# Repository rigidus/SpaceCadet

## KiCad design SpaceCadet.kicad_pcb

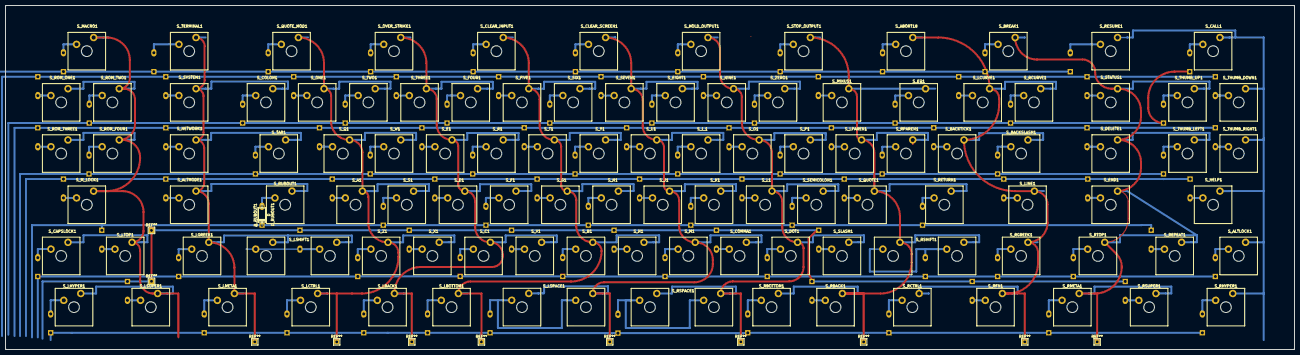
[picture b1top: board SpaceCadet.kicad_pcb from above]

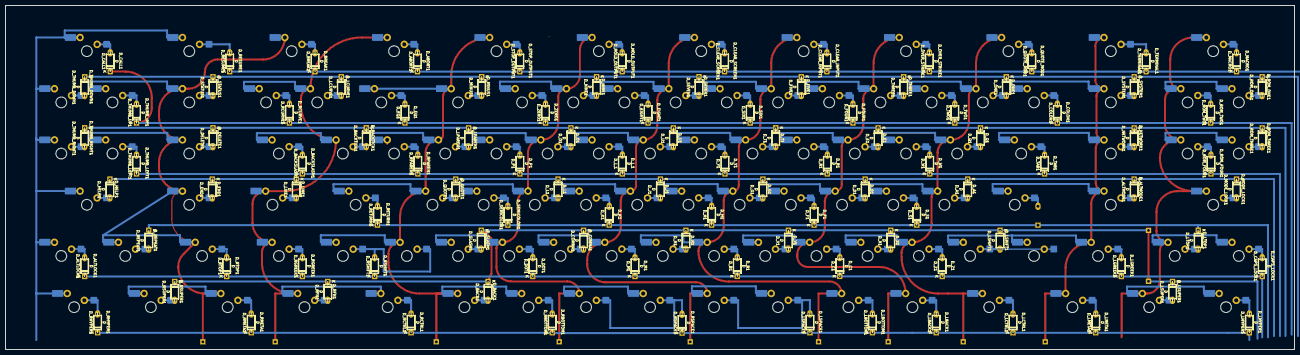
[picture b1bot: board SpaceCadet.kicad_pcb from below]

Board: 2 copper layers, 479.6 x 128.0 mm, 212 parts (105 on the bottom side), 127 nets.

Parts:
D_A1: D; D_P7.62mm
D_ABORT1: D; D_P7.62mm
D_ALTLOCK1: D; D_P7.62mm
D_ALTMODE1: D; D_P7.62mm
D_B1: D; D_P7.62mm
D_BACK1: D; D_P7.62mm
D_BACKSLASH1: D; D_P7.62mm
D_BACKTICK1: D; D_P7.62mm
D_BREAK1: D; D_P7.62mm
D_C1: D; D_P7.62mm
D_CALL1: D; D_P7.62mm
D_CAPS_LOCK1: D; D_P7.62mm
D_CLEAR_INPUT1: D; D_P7.62mm
D_CLEAR_SCREEN1: D; D_P7.62mm
D_COLON1: D; D_P7.62mm
D_COMMA1: D; D_P7.62mm
D_D1: D; D_P7.62mm
D_DELETE1: D; D_P7.62mm
D_DOT1: D; D_P7.62mm
D_E1: D; D_P7.62mm
D_EIGHT1: D; D_P7.62mm
D_END1: D; D_P7.62mm
D_EQ1: D; D_P7.62mm
D_F1: D; D_P7.62mm
D_FIVE1: D; D_P7.62mm
D_FOUR1: D; D_P7.62mm
D_G1: D; D_P7.62mm
D_H1: D; D_P7.62mm
D_HELP1: D; D_P7.62mm
D_HOLD_OUTPUT1: D; D_P7.62mm
D_I_1: D; D_P7.62mm
D_J1: D; D_P7.62mm
D_K1: D; D_P7.62mm
D_L1: D; D_P7.62mm
D_LBACK1: D; D_P7.62mm
D_LBOTTOM1: D; D_P7.62mm
D_LCTRL1: D; D_P7.62mm
D_LCURVE1: D; D_P7.62mm
D_LGREEK1: D; D_P7.62mm
D_LHYPER1: D; D_P7.62mm
D_LINE1: D; D_P7.62mm
D_LMETA1: D; D_P7.62mm
D_LPAREN1: D; D_P7.62mm
D_LSHIFT1: D; D_P7.62mm
D_LSPACE1: D; D_P7.62mm
D_LSUPER1: D; D_P7.62mm
D_LTOP1: D; D_P7.62mm
D_M1: D; D_P7.62mm
D_MACRO1: D; D_P7.62mm
D_MINUS1: D; D_P7.62mm
D_MODE_LOCK1: D; D_P7.62mm
D_N1: D; D_P7.62mm
D_NETWORK1: D; D_P7.62mm
D_NINE1: D; D_P7.62mm
D_O1: D; D_P7.62mm
D_ONE1: D; D_P7.62mm
D_OVER_STRIKE1: D; D_P7.62mm
D_P1: D; D_P7.62mm
D_Q1: D; D_P7.62mm
D_QUOTE1: D; D_P7.62mm
D_QUOTE_MOD1: D; D_P7.62mm
D_R1: D; D_P7.62mm
D_RBOTTOM1: D; D_P7.62mm
D_RCTRL1: D; D_P7.62mm
D_RCURVE1: D; D_P7.62mm
D_REPEAT1: D; D_P7.62mm
D_RESUME1: D; D_P7.62mm
D_RETURN1: D; D_P7.62mm
D_RFN1: D; D_P7.62mm
D_RGREEK1: D; D_P7.62mm
D_RHYPER1: D; D_P7.62mm
D_RMETA1: D; D_P7.62mm
D_ROM_FOUR1: D; D_P7.62mm
D_ROM_ONE1: D; D_P7.62mm
D_ROM_THREE1: D; D_P7.62mm
D_ROM_TWO1: D; D_P7.62mm
D_RPAREN1: D; D_P7.62mm
D_RSHIFT1: D; D_P7.62mm
D_RSPACE1: D; D_P7.62mm
D_RSUPER1: D; D_P7.62mm
D_RTOP1: D; D_P7.62mm
D_RUBOUT1: D; D_P7.62mm
D_S1: D; D_P7.62mm
D_SEMICOLON1: D; D_P7.62mm
D_SEVEN1: D; D_P7.62mm
D_SIX1: D; D_P7.62mm
D_SLASH1: D; D_P7.62mm
D_STATUS1: D; D_P7.62mm
D_STOP_OUTPUT1: D; D_P7.62mm
D_SYSTEM1: D; D_P7.62mm
D_T1: D; D_P7.62mm
D_TAB1: D; D_P7.62mm
D_TERMINAL1: D; D_P7.62mm
D_THREE1: D; D_P7.62mm
D_THUMB_DOWN1: D; D_P7.62mm
D_THUMB_LEFT1: D; D_P7.62mm
D_THUMB_RIGHT1: D; D_P7.62mm
D_THUMB_UP1: D; D_P7.62mm
D_TWO1: D; D_P7.62mm
D_U1: D; D_P7.62mm
D_V1: D; D_P7.62mm
D_W1: D; D_P7.62mm
D_X1: D; D_P7.62mm
D_Y1: D; D_P7.62mm
D_Z1: D; D_P7.62mm
D_ZERO1: D; D_P7.62mm
S_A1: A; SWMXK_1.00u
S_ABORT18: ABORT; SWMXK_2.00u
S_ALTLOCK1: ALT_LOCK; SWMXK_1.00u
S_ALTMODE1: ALTMODE; SWMXK_2.00u
S_B1: B; SWMXK_1.00u
S_BACKSLASH1: BACKSLASH; SWMXK_1.50u
S_BACKTICK1: BACKTICK; SWMXK_1.00u
S_BREAK1: BREAK; SWMXK_2.00u
S_C1: C; SWMXK_1.00u
S_CALL1: CALL; SWMXK_2.00u
S_CAPSLOCK1: CAPS_LOCK; SWMXK_1.00u
S_CLEAR_INPUT1: CLEAR_INPUT; SWMXK_2.00u
S_CLEAR_SCREEN1: CLEAR_SCREEN; SWMXK_2.00u
S_COLON1: COLON; SWMXK_1.00u
S_COMMA1: COMMA; SWMXK_1.00u
S_D1: D; SWMXK_1.00u
S_DELETE1: DELETE; SWMXK_2.00u
S_DOT1: DOT; SWMXK_1.00u
S_E1: E; SWMXK_1.00u
S_EIGHT1: EIGHT; SWMXK_1.00u
S_END1: END1; SWMXK_2.00u
S_EQ1: EQUAL; SWMXK_1.50u
S_F1: F; SWMXK_1.00u
S_FIVE1: FIVE; SWMXK_1.00u
S_FOUR1: FOUR; SWMXK_1.00u
S_G1: G; SWMXK_1.00u
S_H1: H; SWMXK_1.00u
S_HELP1: HELP; SWMXK_2.00u
S_HOLD_OUTPUT1: HOLD_OUTPUT; SWMXK_2.00u
S_I_1: I; SWMXK_1.00u
S_J1: J; SWMXK_1.00u
S_K1: K; SWMXK_1.00u
S_L1: L; SWMXK_1.00u
S_LBACK1: LBACK; SWMXK_1.25u
S_LBOTTOM1: LEFT_BOTTOM; SWMXK_1.25u
S_LCTRL1: LEFT_CTRL; SWMXK_1.75u
S_LCURVE1: LEFT_CURVE; SWMXK_1.00u
S_LGREEK1: LEFT_GREEK; SWMXK_1.50u
S_LHYPER1: LEFT_HYPER; SWMXK_1.50u
S_LINE1: LINE; SWMXK_1.25u
S_LMETA1: LEFT_META; SWMXK_1.50u
S_LPAREN1: LPAREN; SWMXK_1.00u
S_LSHIFT1: LEFT_SHIFT; SWMXK_2.25u
S_LSPACE1: LEFT_SPACE; SWMXK_2.75u
S_LSUPER1: LEFT_SUPER; SWMXK_1.50u
S_LTOP1: LEFT_TOP; SWMXK_1.50u
S_M1: M; SWMXK_1.00u
S_MACRO1: MACRO; SWMXK_2.00u
S_MINUS1: MINUS; SWMXK_1.50u
S_M_LOCK1: MODE_LOCK_1; SWMXK_2.00u
S_N1: N; SWMXK_1.00u
S_NETWORK1: NETWORK; SWMXK_2.00u
S_NINE1: NINE; SWMXK_1.00u
S_O1: O; SWMXK_1.00u
S_ONE1: ONE; SWMXK_1.00u
S_OVER_STRIKE1: OVER_STRIKE; SWMXK_2.00u
S_P1: P; SWMXK_1.00u
S_Q1: Q; SWMXK_1.00u
S_QUOTE1: QUOTE; SWMXK_1.00u
S_QUOTE_MOD1: QUOTE_MOD; SWMXK_2.00u
S_R1: R; SWMXK_1.00u
S_RBACK1: RIGHT_BACK; SWMXK_1.25u
S_RBOTTOM1: RIGHT_BOTTOM; SWMXK_1.25u
S_RCTRL1: RIGHT_CTRL; SWMXK_1.75u
S_RCURVE1: RIGHT_CURVE; SWMXK_1.00u
S_REPEAT1: REPEAT; SWMXK_1.50u
S_RESUME1: RESUME; SWMXK_2.00u
S_RETURN1: RETURN; SWMXK_2.00u
S_RFN1: RIGHT_FN; SWMXK_1.50u
S_RGREEK1: RIGHT_GREEK; SWMXK_1.50u
S_RHYPER1: RIGHT_HYPER; SWMXK_1.50u
S_RMETA1: RIGHT_META; SWMXK_1.50u
S_ROM_FOUR1: ROM_FOUR; SWMXK_1.00u
S_ROM_ONE1: ROM_ONE; SWMXK_1.00u
S_ROM_THREE1: ROM_THREE; SWMXK_1.00u
S_ROM_TWO1: ROM_TWO; SWMXK_1.00u
S_RPAREN1: RPAREN; SWMXK_1.00u
S_RSHIFT1: RIGHT_SHIFT; SWMXK_2.25u
S_RSPACE1: RIGHT_SPACE; SWMXK_2.25u
S_RSUPER1: RIGHT_SUPER; SWMXK_1.50u
S_RTOP1: RIGHT_TOP; SWMXK_1.50u
S_RUBOUT1: RUBOUT; SWMXK_1.75u
S_S1: S; SWMXK_1.00u
S_SEMICOLON1: SEMICOLON; SWMXK_1.00u
S_SEVEN1: SEVEN; SWMXK_1.00u
S_SIX1: SIX; SWMXK_1.00u
S_SLASH1: SLASH; SWMXK_1.00u
S_STATUS1: STATUS; SWMXK_2.00u
S_STOP_OUTPUT1: STOP_OUTPUT; SWMXK_2.00u
S_SYSTEM1: SYSTEM; SWMXK_2.00u
S_T1: T; SWMXK_1.00u
S_TAB1: TAB; SWMXK_1.50u
S_TERMINAL1: TERMINAL; SWMXK_2.00u
S_THREE1: THREE; SWMXK_1.00u
S_THUMB_DOWN1: THUMB_DOWN; SWMXK_1.00u
S_THUMB_LEFT1: THUMB_LEFT; SWMXK_1.00u
S_THUMB_RIGHT1: THUMB_RIGHT; SWMXK_1.00u
S_THUMB_UP1: THUMB_UP; SWMXK_1.00u
S_TWO1: TWO; SWMXK_1.00u
S_U1: U; SWMXK_1.00u
S_V1: V; SWMXK_1.00u
S_W1: W; SWMXK_1.00u
S_X1: X; SWMXK_1.00u
S_Y1: Y; SWMXK_1.00u
S_Z1: Z; SWMXK_1.00u
S_ZERO1: ZERO; SWMXK_1.00u

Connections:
COL1: S_CAPSLOCK1.1 (in), S_LHYPER1.1 (in), S_LSUPER1.1 (in), S_LTOP1.1 (in), S_MACRO1.1 (in), S_M_LOCK1.1 (in), S_ROM_FOUR1.1 (in), S_ROM_ONE1.1 (in), S_ROM_THREE1.1 (in), S_ROM_TWO1.1 (in)
COL2: S_ALTMODE1.1 (in), S_COLON1.1 (in), S_LGREEK1.1 (in), S_LMETA1.1 (in), S_LSHIFT1.1 (in), S_NETWORK1.1 (in), S_RUBOUT1.1 (in), S_SYSTEM1.1 (in), S_TAB1.1 (in), S_TERMINAL1.1 (in)
COL3: S_A1.1 (in), S_LCTRL1.1 (in), S_ONE1.1 (in), S_Q1.1 (in), S_QUOTE_MOD1.1 (in), S_S1.1 (in), S_TWO1.1 (in), S_W1.1 (in), S_X1.1 (in), S_Z1.1 (in)
COL4: S_C1.1 (in), S_D1.1 (in), S_E1.1 (in), S_F1.1 (in), S_FOUR1.1 (in), S_LBACK1.1 (in), S_OVER_STRIKE1.1 (in), S_R1.1 (in), S_THREE1.1 (in), S_V1.1 (in)
COL5: S_B1.1 (in), S_CLEAR_INPUT1.1 (in), S_FIVE1.1 (in), S_G1.1 (in), S_H1.1 (in), S_LBOTTOM1.1 (in), S_N1.1 (in), S_SIX1.1 (in), S_T1.1 (in), S_Y1.1 (in)
COL6: S_CLEAR_SCREEN1.1 (in), S_COMMA1.1 (in), S_EIGHT1.1 (in), S_I_1.1 (in), S_J1.1 (in), S_K1.1 (in), S_LSPACE1.1 (in), S_M1.1 (in), S_SEVEN1.1 (in), S_U1.1 (in)
COL7: S_DOT1.1 (in), S_HOLD_OUTPUT1.1 (in), S_L1.1 (in), S_NINE1.1 (in), S_O1.1 (in), S_P1.1 (in), S_RSPACE1.1 (in), S_SEMICOLON1.1 (in), S_SLASH1.1 (in), S_ZERO1.1 (in)
COL8: S_EQ1.1 (in), S_LPAREN1.1 (in), S_MINUS1.1 (in), S_QUOTE1.1 (in), S_RBACK1.1 (in), S_RBOTTOM1.1 (in), S_RETURN1.1 (in), S_RPAREN1.1 (in), S_RSHIFT1.1 (in), S_STOP_OUTPUT1.1 (in)
COL9: S_ABORT18.1 (in), S_BACKSLASH1.1 (in), S_BACKTICK1.1 (in), S_LCURVE1.1 (in), S_LINE1.1 (in), S_RCTRL1.1 (in), S_RCURVE1.1 (in), S_RFN1.1 (in), S_RGREEK1.1 (in)
COL10: S_BREAK1.1 (in), S_DELETE1.1 (in), S_END1.1 (in), S_REPEAT1.1 (in), S_RMETA1.1 (in), S_RSUPER1.1 (in), S_RTOP1.1 (in), S_STATUS1.1 (in), S_THUMB_LEFT1.1 (in), S_THUMB_UP1.1 (in)
COL11: S_ALTLOCK1.1 (in), S_CALL1.1 (in), S_HELP1.1 (in), S_RESUME1.1 (in), S_RHYPER1.1 (in), S_THUMB_DOWN1.1 (in), S_THUMB_RIGHT1.1 (in)
unnamed: D_A1.2 (A), S_A1.2 (out)
unnamed: D_ABORT1.2 (A), S_ABORT18.2 (out)
unnamed: D_ALTLOCK1.2 (A), S_ALTLOCK1.2 (out)
unnamed: D_ALTMODE1.2 (A), S_ALTMODE1.2 (out)
unnamed: D_B1.2 (A), S_B1.2 (out)
unnamed: D_BACK1.2 (A), S_RBACK1.2 (out)
unnamed: D_BACKSLASH1.2 (A), S_BACKSLASH1.2 (out)
unnamed: D_BACKTICK1.2 (A), S_BACKTICK1.2 (out)
unnamed: D_BREAK1.2 (A), S_BREAK1.2 (out)
unnamed: D_C1.2 (A), S_C1.2 (out)
unnamed: D_CALL1.2 (A), S_CALL1.2 (out)
unnamed: D_CAPS_LOCK1.2 (A), S_CAPSLOCK1.2 (out)
unnamed: D_CLEAR_INPUT1.2 (A), S_CLEAR_INPUT1.2 (out)
unnamed: D_CLEAR_SCREEN1.2 (A), S_CLEAR_SCREEN1.2 (out)
unnamed: D_COLON1.2 (A), S_COLON1.2 (out)
unnamed: D_COMMA1.2 (A), S_COMMA1.2 (out)
unnamed: D_D1.2 (A), S_D1.2 (out)
unnamed: D_DELETE1.2 (A), S_DELETE1.2 (out)
unnamed: D_DOT1.2 (A), S_DOT1.2 (out)
unnamed: D_E1.2 (A), S_E1.2 (out)
unnamed: D_EIGHT1.2 (A), S_EIGHT1.2 (out)
unnamed: D_END1.2 (A), S_END1.2 (out)
unnamed: D_EQ1.2 (A), S_EQ1.2 (out)
unnamed: D_F1.2 (A), S_F1.2 (out)
unnamed: D_FIVE1.2 (A), S_FIVE1.2 (out)
unnamed: D_FOUR1.2 (A), S_FOUR1.2 (out)
unnamed: D_G1.2 (A), S_G1.2 (out)
unnamed: D_H1.2 (A), S_H1.2 (out)
unnamed: D_HELP1.2 (A), S_HELP1.2 (out)
unnamed: D_HOLD_OUTPUT1.2 (A), S_HOLD_OUTPUT1.2 (out)
unnamed: D_I_1.2 (A), S_I_1.2 (out)
unnamed: D_J1.2 (A), S_J1.2 (out)
unnamed: D_K1.2 (A), S_K1.2 (out)
unnamed: D_L1.2 (A), S_L1.2 (out)
unnamed: D_LBACK1.2 (A), S_LBACK1.2 (out)
unnamed: D_LBOTTOM1.2 (A), S_LBOTTOM1.2 (out)
unnamed: D_LCTRL1.2 (A), S_LCTRL1.2 (out)
unnamed: D_LCURVE1.2 (A), S_LCURVE1.2 (out)
unnamed: D_LGREEK1.2 (A), S_LGREEK1.2 (out)
unnamed: D_LHYPER1.2 (A), S_LHYPER1.2 (out)
unnamed: D_LINE1.2 (A), S_LINE1.2 (out)
unnamed: D_LMETA1.2 (A), S_LMETA1.2 (out)
unnamed: D_LPAREN1.2 (A), S_LPAREN1.2 (out)
unnamed: D_LSHIFT1.2 (A), S_LSHIFT1.2 (out)
unnamed: D_LSPACE1.2 (A), S_LSPACE1.2 (out)
unnamed: D_LSUPER1.2 (A), S_LSUPER1.2 (out)
unnamed: D_LTOP1.2 (A), S_LTOP1.2 (out)
unnamed: D_M1.2 (A), S_M1.2 (out)
unnamed: D_MACRO1.2 (A), S_MACRO1.2 (out)
unnamed: D_MINUS1.2 (A), S_MINUS1.2 (out)
unnamed: D_MODE_LOCK1.2 (A), S_M_LOCK1.2 (out)
unnamed: D_N1.2 (A), S_N1.2 (out)
unnamed: D_NETWORK1.2 (A), S_NETWORK1.2 (out)
unnamed: D_NINE1.2 (A), S_NINE1.2 (out)
unnamed: D_O1.2 (A), S_O1.2 (out)
unnamed: D_ONE1.2 (A), S_ONE1.2 (out)
unnamed: D_OVER_STRIKE1.2 (A), S_OVER_STRIKE1.2 (out)
unnamed: D_P1.2 (A), S_P1.2 (out)
unnamed: D_Q1.2 (A), S_Q1.2 (out)
unnamed: D_QUOTE1.2 (A), S_QUOTE1.2 (out)
unnamed: D_QUOTE_MOD1.2 (A), S_QUOTE_MOD1.2 (out)
unnamed: D_R1.2 (A), S_R1.2 (out)
unnamed: D_RBOTTOM1.2 (A), S_RBOTTOM1.2 (out)
unnamed: D_RCTRL1.2 (A), S_RCTRL1.2 (out)
unnamed: D_RCURVE1.2 (A), S_RCURVE1.2 (out)
unnamed: D_REPEAT1.2 (A), S_REPEAT1.2 (out)
unnamed: D_RESUME1.2 (A), S_RESUME1.2 (out)
unnamed: D_RETURN1.2 (A), S_RETURN1.2 (out)
unnamed: D_RFN1.2 (A), S_RFN1.2 (out)
unnamed: D_RGREEK1.2 (A), S_RGREEK1.2 (out)
unnamed: D_RHYPER1.2 (A), S_RHYPER1.2 (out)
unnamed: D_RMETA1.2 (A), S_RMETA1.2 (out)
unnamed: D_ROM_FOUR1.2 (A), S_ROM_FOUR1.2 (out)
unnamed: D_ROM_ONE1.2 (A), S_ROM_ONE1.2 (out)
unnamed: D_ROM_THREE1.2 (A), S_ROM_THREE1.2 (out)
unnamed: D_ROM_TWO1.2 (A), S_ROM_TWO1.2 (out)
unnamed: D_RPAREN1.2 (A), S_RPAREN1.2 (out)
unnamed: D_RSHIFT1.2 (A), S_RSHIFT1.2 (out)
unnamed: D_RSPACE1.2 (A), S_RSPACE1.2 (out)
unnamed: D_RSUPER1.2 (A), S_RSUPER1.2 (out)
unnamed: D_RTOP1.2 (A), S_RTOP1.2 (out)
unnamed: D_RUBOUT1.2 (A), S_RUBOUT1.2 (out)
unnamed: D_S1.2 (A), S_S1.2 (out)
unnamed: D_SEMICOLON1.2 (A), S_SEMICOLON1.2 (out)
unnamed: D_SEVEN1.2 (A), S_SEVEN1.2 (out)
unnamed: D_SIX1.2 (A), S_SIX1.2 (out)
unnamed: D_SLASH1.2 (A), S_SLASH1.2 (out)
unnamed: D_STATUS1.2 (A), S_STATUS1.2 (out)
unnamed: D_STOP_OUTPUT1.2 (A), S_STOP_OUTPUT1.2 (out)
unnamed: D_SYSTEM1.2 (A), S_SYSTEM1.2 (out)
unnamed: D_T1.2 (A), S_T1.2 (out)
unnamed: D_TAB1.2 (A), S_TAB1.2 (out)
unnamed: D_TERMINAL1.2 (A), S_TERMINAL1.2 (out)
unnamed: D_THREE1.2 (A), S_THREE1.2 (out)
unnamed: D_THUMB_DOWN1.2 (A), S_THUMB_DOWN1.2 (out)
unnamed: D_THUMB_LEFT1.2 (A), S_THUMB_LEFT1.2 (out)
unnamed: D_THUMB_RIGHT1.2 (A), S_THUMB_RIGHT1.2 (out)
unnamed: D_THUMB_UP1.2 (A), S_THUMB_UP1.2 (out)
unnamed: D_TWO1.2 (A), S_TWO1.2 (out)
unnamed: D_U1.2 (A), S_U1.2 (out)
unnamed: D_V1.2 (A), S_V1.2 (out)
unnamed: D_W1.2 (A), S_W1.2 (out)
unnamed: D_X1.2 (A), S_X1.2 (out)
unnamed: D_Y1.2 (A), S_Y1.2 (out)
unnamed: D_Z1.2 (A), S_Z1.2 (out)
unnamed: D_ZERO1.2 (A), S_ZERO1.2 (out)
ROW1: D_ABORT1.1 (K), D_BREAK1.1 (K), D_CLEAR_INPUT1.1 (K), D_CLEAR_SCREEN1.1 (K), D_HOLD_OUTPUT1.1 (K), D_MACRO1.1 (K), D_OVER_STRIKE1.1 (K), D_QUOTE_MOD1.1 (K), D_RESUME1.1 (K), D_STOP_OUTPUT1.1 (K), D_TERMINAL1.1 (K)
ROW2: D_FIVE1.1 (K), D_LCURVE1.1 (K), D_MINUS1.1 (K), D_NINE1.1 (K), D_ONE1.1 (K), D_ROM_ONE1.1 (K), D_SEVEN1.1 (K), D_STATUS1.1 (K), D_SYSTEM1.1 (K), D_THREE1.1 (K), D_THUMB_DOWN1.1 (K)
ROW3: D_BACKTICK1.1 (K), D_DELETE1.1 (K), D_E1.1 (K), D_LPAREN1.1 (K), D_NETWORK1.1 (K), D_O1.1 (K), D_Q1.1 (K), D_ROM_THREE1.1 (K), D_T1.1 (K), D_THUMB_RIGHT1.1 (K), D_U1.1 (K)
ROW4: D_A1.1 (K), D_ALTMODE1.1 (K), D_D1.1 (K), D_END1.1 (K), D_G1.1 (K), D_HELP1.1 (K), D_J1.1 (K), D_L1.1 (K), D_LINE1.1 (K), D_MODE_LOCK1.1 (K), D_QUOTE1.1 (K)
ROW5: D_ALTLOCK1.1 (K), D_B1.1 (K), D_C1.1 (K), D_CAPS_LOCK1.1 (K), D_DOT1.1 (K), D_LGREEK1.1 (K), D_M1.1 (K), D_RGREEK1.1 (K), D_RSHIFT1.1 (K), D_RTOP1.1 (K), D_Z1.1 (K)
ROW6: D_LBACK1.1 (K), D_LBOTTOM1.1 (K), D_LCTRL1.1 (K), D_LHYPER1.1 (K), D_LMETA1.1 (K), D_LSPACE1.1 (K), D_RBOTTOM1.1 (K), D_RCTRL1.1 (K), D_RHYPER1.1 (K), D_RMETA1.1 (K), D_RSPACE1.1 (K)
ROW7: D_BACK1.1 (K), D_COMMA1.1 (K), D_LSHIFT1.1 (K), D_LSUPER1.1 (K), D_N1.1 (K), D_RFN1.1 (K), D_RSUPER1.1 (K), D_SLASH1.1 (K), D_V1.1 (K), D_X1.1 (K)
ROW8: D_F1.1 (K), D_H1.1 (K), D_K1.1 (K), D_LTOP1.1 (K), D_REPEAT1.1 (K), D_RETURN1.1 (K), D_RUBOUT1.1 (K), D_S1.1 (K), D_SEMICOLON1.1 (K)
ROW9: D_BACKSLASH1.1 (K), D_I_1.1 (K), D_P1.1 (K), D_R1.1 (K), D_ROM_FOUR1.1 (K), D_RPAREN1.1 (K), D_TAB1.1 (K), D_THUMB_LEFT1.1 (K), D_W1.1 (K), D_Y1.1 (K)
ROW10: D_CALL1.1 (K), D_COLON1.1 (K), D_EIGHT1.1 (K), D_EQ1.1 (K), D_FOUR1.1 (K), D_RCURVE1.1 (K), D_ROM_TWO1.1 (K), D_SIX1.1 (K), D_THUMB_UP1.1 (K), D_TWO1.1 (K), D_ZERO1.1 (K)

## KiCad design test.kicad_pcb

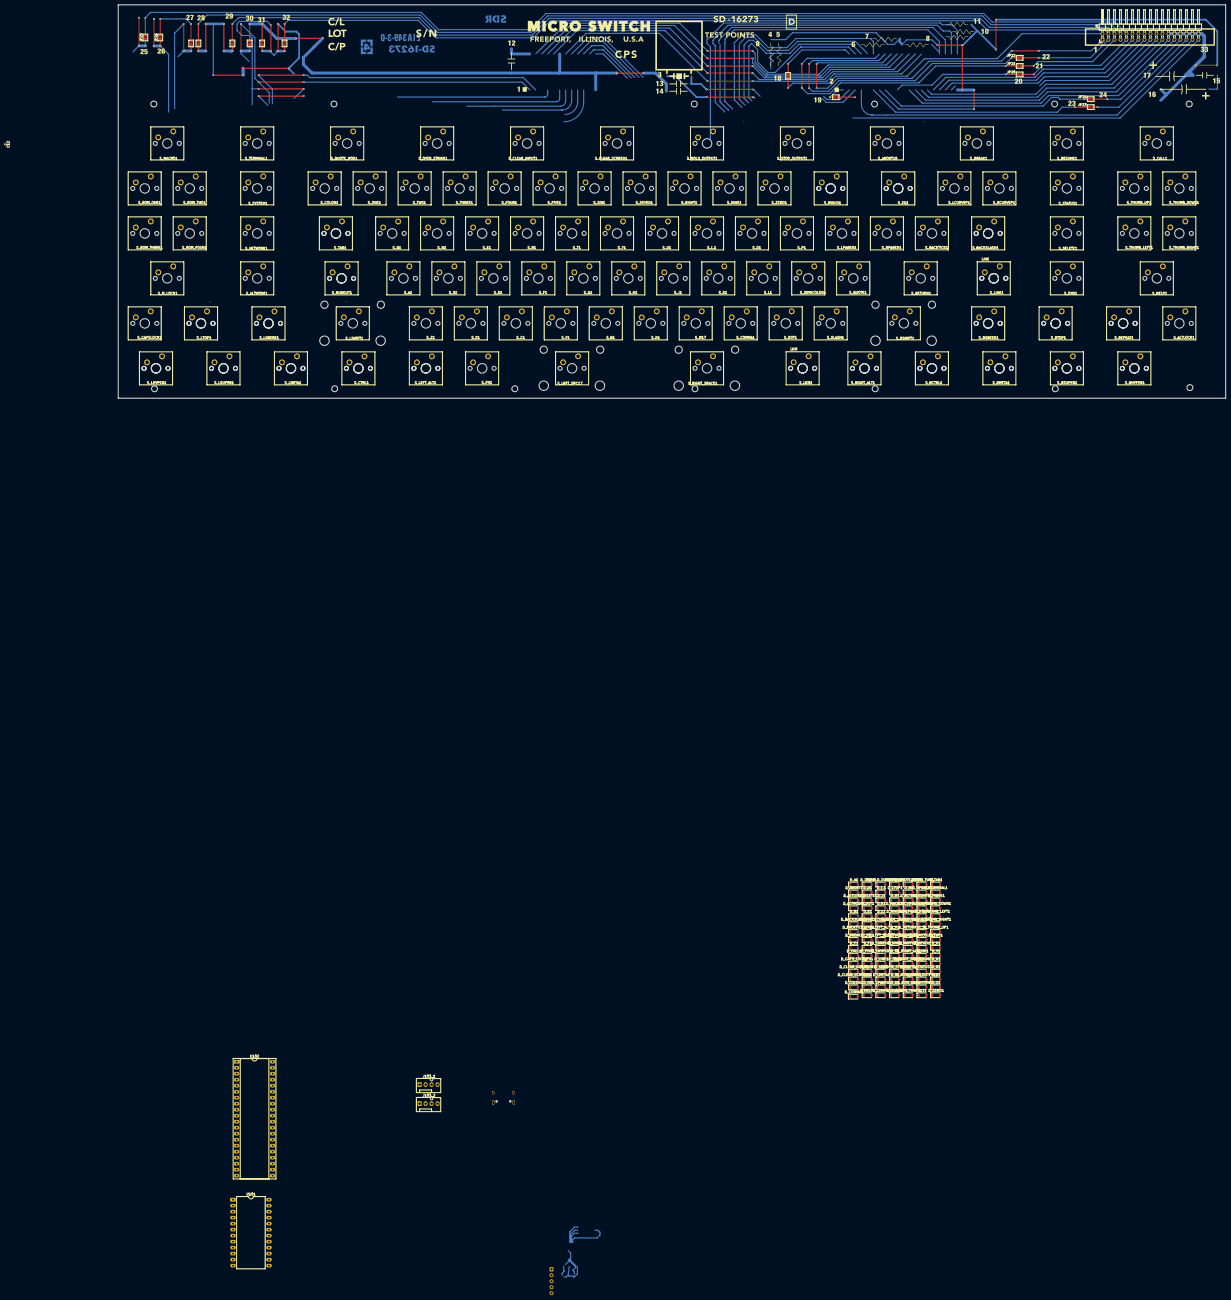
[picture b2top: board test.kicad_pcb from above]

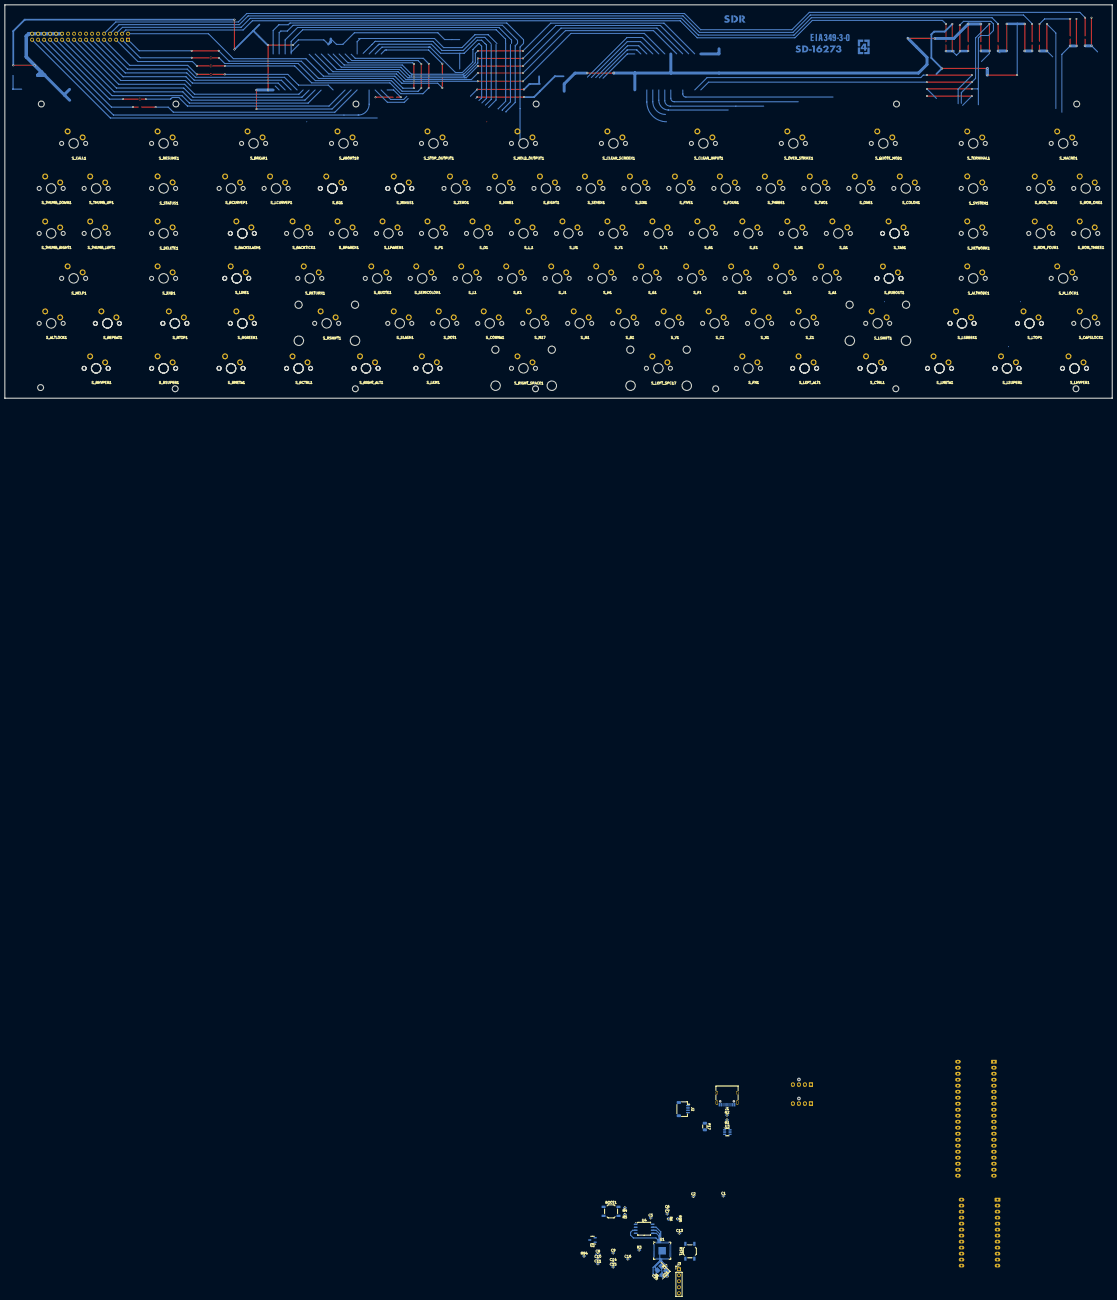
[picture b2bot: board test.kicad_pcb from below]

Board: 2 copper layers, 469.0 x 166.6 mm, 266 parts (35 on the bottom side), 69 nets.

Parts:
BOOT1: SW_Push; SW_SPST_TL3342
C1, C2, C5, C6, C9: 1u; C_0402_1005Metric
C7, C10, C11, C12, C13, C14, C15, C16: 100n; C_0402_1005Metric
C8: 10u; C_0603_1608Metric
C20, C21: 22p; C_0402_1005Metric
D_A1: D; D_SOD-123
D_ABORT1: D; D_SOD-123
D_ALTLOCK1: D; D_SOD-123
D_ALTMODE1: D; D_SOD-123
D_B1: D; D_SOD-123
D_BACKSLASH1: D; D_SOD-123
D_BACKTICK1: D; D_SOD-123
D_BREAK1: D; D_SOD-123
D_C1: D; D_SOD-123
D_CALL1: D; D_SOD-123
D_CAPS_LOCK1: D; D_SOD-123
D_CLEAR_INPUT1: D; D_SOD-123
D_CLEAR_SCREEN1: D; D_SOD-123
D_COLON1: D; D_SOD-123
D_COMMA1: D; D_SOD-123
D_CTRL1: D; D_SOD-123
D_D1: D; D_SOD-123
D_DELETE1: D; D_SOD-123
D_DOT1: D; D_SOD-123
D_E1: D; D_SOD-123
D_EIGHT1: D; D_SOD-123
D_END1: D; D_SOD-123
D_EQ1: D; D_SOD-123
D_F1: D; D_SOD-123
D_FIVE1: D; D_SOD-123
D_FN1: D; D_SOD-123
D_FOUR1: D; D_SOD-123
D_G1: D; D_SOD-123
D_H1: D; D_SOD-123
D_HELP1: D; D_SOD-123
D_HOLD_OUTPUT1: D; D_SOD-123
D_I_1: D; D_SOD-123
D_J1: D; D_SOD-123
D_K1: D; D_SOD-123
D_L1: D; D_SOD-123
D_LCURVEP1: D; D_SOD-123
D_LEFT_ALT1: D; D_SOD-123
D_LEFT_SPC17: D; D_SOD-123
D_LGREEK1: D; D_SOD-123
D_LHYPER1: D; D_SOD-123
D_LINE1: D; D_SOD-123
D_LKM1: D; D_SOD-123
D_LMETA1: D; D_SOD-123
D_LPAREN1: D; D_SOD-123
D_LSHIFT1: D; D_SOD-123
D_LSUPER1: D; D_SOD-123
D_LTOP1: D; D_SOD-123
D_M1: D; D_SOD-123
D_MACRO1: D; D_SOD-123
D_MINUS1: D; D_SOD-123
D_MODE_LOCK1: D; D_SOD-123
D_N1: D; D_SOD-123
D_NETWORK1: D; D_SOD-123
D_NINE1: D; D_SOD-123
D_O1: D; D_SOD-123
D_ONE1: D; D_SOD-123
D_OVER_STRIKE1: D; D_SOD-123
D_P1: D; D_SOD-123
D_Q1: D; D_SOD-123
D_QUOTE1: D; D_SOD-123
D_QUOTE_MOD1: D; D_SOD-123
D_R1: D; D_SOD-123
D_RCTRL1: D; D_SOD-123
D_RCURVEP1: D; D_SOD-123
D_REPEAT1: D; D_SOD-123
D_RESUME1: D; D_SOD-123
D_RETURN1: D; D_SOD-123
D_RGREEK1: D; D_SOD-123
D_RHYPER1: D; D_SOD-123
D_RIGHT_ALT1: D; D_SOD-123
D_RIGHT_SPACE1: D; D_SOD-123
D_RMETA1: D; D_SOD-123
D_ROM_FOUR1: D; D_SOD-123
D_ROM_ONE1: D; D_SOD-123
D_ROM_THREE1: D; D_SOD-123
D_ROM_TWO1: D; D_SOD-123
D_RPAREN1: D; D_SOD-123
D_RSHIFT1: D; D_SOD-123
D_RSUPER1: D; D_SOD-123
D_RTOP1: D; D_SOD-123
D_RUBOUT1: D; D_SOD-123
D_S1: D; D_SOD-123
D_SEMICOLON1: D; D_SOD-123
D_SEVEN1: D; D_SOD-123
D_SIX1: D; D_SOD-123
D_SLASH1: D; D_SOD-123
D_STATUS1: D; D_SOD-123
D_STOP_OUTPUT1: D; D_SOD-123
D_SYSTEM1: D; D_SOD-123
D_T1: D; D_SOD-123
D_TAB1: D; D_SOD-123
D_TERMINAL1: D; D_SOD-123
D_THREE1: D; D_SOD-123
D_THUMB_DOWN1: D; D_SOD-123
D_THUMB_LEFT1: D; D_SOD-123
D_THUMB_RIGHT1: D; D_SOD-123
D_THUMB_UP1: D; D_SOD-123
D_TWO1: D; D_SOD-123
D_U1: D; D_SOD-123
D_V1: D; D_SOD-123
D_W1: D; D_SOD-123
D_X1: D; D_SOD-123
D_Y1: D; D_SOD-123
D_Z1: D; D_SOD-123
D_ZERO1: D; D_SOD-123
F17: Fuse_Small; Fuse_1206_3216Metric
J0: Conn_02x17_Odd_Even; PinHeader_2x17_P2.54mm_Horizontal
J1: USB_C_Receptacle_USB2.0_16P; USB_C_Receptacle_HRO_TYPE-C-31-M-12
J2: Conn_01x04; JST_SH_SM04B-SRSS-TB_1x04-1MP_P1.00mm_Horizontal
J3: Conn_01x05; PinHeader_1x05_P2.54mm_Vertical
J103_1, J103_2: Conn_01x04; FanPinHeader_1x04_P2.54mm_Vertical
JP18, JP19, JP23, JP25, JP26, JP27, JP28, JP29, JP30, JP31, JP32: Jumper Open; SolderJumper-2_P1.3mm_Open_TrianglePad1.0x1.5mm
JP20, JP21, JP22, JP24: Jumper Bridged; SolderJumper-2_P1.3mm_Bridged2Bar_Pad1.0x1.5mm
R1, R2, R3, R4, R5: 5.1k; R_0402_1005Metric
R6, R7: 1k; R_0402_1005Metric
R94, R95: 27; R_0402_1005Metric
RST1: SW_Push; SW_SPST_TL3342
S_A1: A; SW_MX_1U
S_ABORT18: ABORT; SW_MX_2U
S_ALTLOCK1: ALT_LOCK; SW_MX_1U
S_ALTMODE1: ALTMODE; SW_MX_2U
S_B1: B; SW_MX_1U
S_BACKSLASH1: BACKSLASH; SW_MX_1.5U
S_BACKTICK1: BACKTICK; SW_MX_1U
S_BREAK1: BREAK; SW_MX_2U
S_C1: C; SW_MX_1U
S_CALL1: CALL; SW_MX_2U
S_CAPSLOCK1: CAPS_LOCK; SW_MX_1U
S_CLEAR_INPUT1: CLEAR_INPUT; SW_MX_2U
S_CLEAR_SCREEN1: CLEAR_SCREEN; SW_MX_2U
S_COLON1: COLON; SW_MX_1U
S_COMMA1: COMMA; SW_MX_1U
S_CTRL1: LEFT_CTRL; SW_MX_1.5U
S_D1: D; SW_MX_1U
S_DELETE1: DELETE; SW_MX_2U
S_DOT1: DOT; SW_MX_1U
S_E1: E; SW_MX_1U
S_EIGHT1: EIGHT; SW_MX_1U
S_END1: END1; SW_MX_2U
S_EQ1: EQ; SW_MX_1.5U
S_F1: F; SW_MX_1U
S_FIVE1: FIVE; SW_MX_1U
S_FN1: FN; SW_MX_1U
S_FOUR1: FOUR; SW_MX_1U
S_G1: G; SW_MX_1U
S_H1: H; SW_MX_1U
S_HELP1: HELP; SW_MX_2U
S_HOLD_OUTPUT1: HOLD_OUTPUT; SW_MX_2U
S_I_1: I; SW_MX_1U
S_J1: J; SW_MX_1U
S_K1: K; SW_MX_1U
S_L1: L; SW_MX_1U
S_LCURVEP1: LCURVEP; SW_MX_1U
S_LEFT_ALT1: LEFT_ALT; SW_MX_1.5U
S_LEFT_SPC17: LEFT_SPACE; SW_MX_3U
S_LGREEK1: LEFT_GREEK; SW_MX_1.5U
S_LHYPER1: LEFT_HYPER; SW_MX_1.5U
S_LINE1: LINE; SW_MX_1.25U
S_LKM1: LKM; SW_MX_1.25U
S_LMETA1: LEFT_META; SW_MX_1.5U
S_LPAREN1: LPAREN; SW_MX_1U
S_LSHIFT1: LEFT_SHIFT; SW_MX_2.25U
S_LSUPER1: LEFT_SUPER; SW_MX_1.5U
S_LTOP1: LEFT_TOP; SW_MX_1.5U
S_M17: M; SW_MX_1U
S_MACRO1: MACRO; SW_MX_2U
S_MINUS1: MINUS; SW_MX_1.5U
S_M_LOCK1: MODE_LOCK_1; SW_MX_2U
S_N1: N; SW_MX_1U
S_NETWORK1: NETWORK; SW_MX_2U
S_NINE1: NINE; SW_MX_1U
S_O1: O; SW_MX_1U
S_ONE1: ONE; SW_MX_1U
S_OVER_STRIKE1: OVER_STRIKE; SW_MX_2U
S_P1: P; SW_MX_1U
S_Q1: Q; SW_MX_1U
S_QUOTE1: QUOTE; SW_MX_1U
S_QUOTE_MOD1: QUOTE_MOD; SW_MX_2U
S_R1: R; SW_MX_1U
S_RCTRL1: RIGHT_CTRL; SW_MX_1.5U
S_RCURVEP1: RCURVEP; SW_MX_1U
S_REPEAT1: REPEAT; SW_MX_1.5U
S_RESUME1: RESUME; SW_MX_2U
S_RETURN1: RETURN; SW_MX_2U
S_RGREEK1: RIGHT_GREEK; SW_MX_1.5U
S_RHYPER1: RIGHT_HYPER; SW_MX_1.5U
S_RIGHT_ALT1: RIGHT_ALT; SW_MX_1.5U
S_RIGHT_SPACE1: RIGHT_SPACE; SW_MX_3U
S_RMETA1: RIGHT_META; SW_MX_1.5U
S_ROM_FOUR1: ROM_FOUR; SW_MX_1U
S_ROM_ONE1: ROM_ONE; SW_MX_1U
S_ROM_THREE1: ROM_THREE; SW_MX_1U
S_ROM_TWO1: ROM_TWO; SW_MX_1U
S_RPAREN1: RPAREN; SW_MX_1U
S_RSHIFT1: RIGHT_SHIFT; SW_MX_2.25U
S_RSUPER1: RIGHT_SUPER; SW_MX_1.5U
S_RTOP1: RIGHT_TOP; SW_MX_1.5U
S_RUBOUT1: RUBOUT; SW_MX_1.75U
S_S1: S; SW_MX_1U
S_SEMICOLON1: SEMICOLON; SW_MX_1U
S_SEVEN1: SEVEN; SW_MX_1U
S_SIX1: SIX; SW_MX_1U
S_SLASH1: SLASH; SW_MX_1U
S_STATUS1: STATUS; SW_MX_2U
S_STOP_OUTPUT1: STOP_OUTPUT; SW_MX_2U
S_SYSTEM1: SYSTEM; SW_MX_2U
S_T1: T; SW_MX_1U
S_TAB1: TAB; SW_MX_1.5U
S_TERMINAL1: TERMINAL; SW_MX_2U
S_THREE1: THREE; SW_MX_1U
S_THUMB_DOWN1: THUMB_DOWN; SW_MX_1U
S_THUMB_LEFT1: THUMB_LEFT; SW_MX_1U
S_THUMB_RIGHT1: THUMB_RIGHT; SW_MX_1U
S_THUMB_UP1: THUMB_UP; SW_MX_1U
S_TWO1: TWO; SW_MX_1U
S_U1: U; SW_MX_1U
S_V1: V; SW_MX_1U
S_W1: W; SW_MX_1U
S_X1: X; SW_MX_1U
S_Y1: Y; SW_MX_1U
S_Z1: Z; SW_MX_1U
S_ZERO1: ZERO; SW_MX_1U
U1: RP2040; QFN-56-1EP_7x7mm_P0.4mm_EP3.2x3.2mm
U2: XC6206PxxxMR; SOT-23-3
U3: SRV05-4; SOT-23-6
U4: W25Q128JVS; SOIC-8_5.23x5.23mm_P1.27mm
U101: 74LS154; DIP-24_W15.24mm_LongPads
U102: 8048; DIP-40_W15.24mm_Socket_LongPads
Y1: Crystal_GND24; Crystal_SMD_3225-4Pin_3.2x2.5mm_HandSoldering

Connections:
+1V1: C6.1, C7.1, C13.1, U1.23 (DVDD), U1.45 (VREG_VOUT), U1.50 (DVDD)
+3V3: C2.1, C5.1, C8.1, C9.1, C10.1, C11.1, C12.1, C14.1, C15.1, C16.1, J3.2, R3.2, R4.2, U1.1 (IOVDD), U1.10 (IOVDD), U1.22 (IOVDD), U1.33 (IOVDD), U1.42 (IOVDD), U1.43 (ADC_AVDD), U1.44 (VREG_IN), U1.48 (USB_VDD), U1.49 (IOVDD), U2.2 (VO), U4.8 (VCC)
+5V: C1.1, F17.2, J0.20, J0.22, J2.1, U2.3 (VI), U3.5 (VP), U101.24 (VCC), U102.5 (~SS), U102.26 (VDD), U102.40 (VCC)
/A0: U101.18 (E0), U102.27 (P1.0)
/A1: U101.20 (A3), U102.28 (P1.1)
/A2: U101.21 (A2), U102.29 (P1.2)
/A3: U101.22 (A1), U102.30 (P1.3)
/A4: U101.23 (A0), U102.31 (P1.4)
/DB0: J0.25, U102.12 (DB.0)
/DB1: J0.23, U102.13 (DB.1)
/DB2: J0.21, U102.14 (DB.2)
/DB3: J0.19, U102.15 (DB.3)
/DB4: J0.11, U102.16 (DB.4)
/DB5: J0.13, U102.17 (DB.5)
/DB6: J0.15, U102.18 (DB.6)
/DB7: J0.17, U102.19 (DB.7)
A5: J0.1, U102.32 (P1.5)
A6: JP22.1 (A), U102.33 (P1.6)
A7: JP21.1 (A), U102.34 (P1.7)
COL0: JP30.1 (A), U101.1 (S0)
COL1: JP27.1 (A), U101.2 (S1)
COL2: JP31.1 (A), U101.3 (S2)
COL4: JP26.1 (A), U101.5 (S4)
CONN2: J0.2, JP18.2 (B)
CONN3: J0.3, JP22.2 (B)
CONN4: J0.4, JP32.2 (B)
CONN5: J0.5, JP21.2 (B)
CONN6: J0.6, JP29.2 (B)
CONN8: J0.8, JP28.2 (B)
CONN9: J0.9, JP20.2 (B)
CONN10: J0.10, JP25.2 (B)
CONN27: J0.27, JP24.2 (B)
CONN29: J0.29, JP23.2 (B)
CONN33: J0.33, JP19.2 (B)
D+: J1.A6 (D+), J1.B6 (D+), J2.3, R94.1, U3.1 (IO1)
D-: J1.A7 (D-), J1.B7 (D-), J2.2, R95.1, U3.3 (IO2)
GND: BOOT1.1, C1.2, C2.2, C5.2, C6.2, C7.2, C8.2, C9.2, C10.2, C11.2, C12.2, C13.2, C14.2, C15.2, C16.2, C20.1, C21.1, J0.24, J0.26, J0.28, J0.30, J0.32, J0.34, J1.A1 (GND), J1.A12 (GND), J1.B1 (GND), J1.B12 (GND), J1.S1 (SHIELD), J2.4, J3.3, JP26.2 (B), JP27.2 (B), JP30.2 (B), JP31.2 (B), R1.2, R2.2, RST1.1, U1.19 (TESTEN), U1.57 (GND), U2.1 (GND), U3.2 (VN), U4.4 (GND), U101.12 (GND), U101.19 (E1), U102.7 (EA), U102.20 (GND), Y1.2, Y1.4
INT: JP23.1 (A), U102.6 (~INT)
unnamed: BOOT1.2, R6.1
unnamed: C21.2, R7.1, Y1.1
unnamed: J1.A5 (CC1), R2.1
unnamed: J1.B5 (CC2), R1.1
unnamed: R4.1, R5.2
unnamed: R95.2, U1.46 (USB_DM)
unnamed: R94.2, U1.47 (USB_DP)
Q_CLK: U1.52 (QSPI_SCLK), U4.6 (CLK)
Q_IO0: U1.53 (QSPI_SD0), U4.5 (DI(IO0))
Q_IO1: U1.55 (QSPI_SD1), U4.2 (DO(IO1))
Q_IO2: U1.54 (QSPI_SD2), U4.3 (IO2)
Q_IO3: U1.51 (QSPI_SD3), U4.7 (IO3)
Q_SEL: R5.1, R6.2, U1.56 (QSPI_SS), U4.1 (~CS)
READ: JP24.1 (A), U102.8 (~RD)
RESET: J0.31, J3.1, R3.1, RST1.2, U1.26 (RUN), U102.4 (~RESET)
ROW0: J103_1.1, JP28.1 (A), JP29.1 (A), JP32.1 (A), U102.21 (P2.0)
ROW1: J103_1.2, U102.22 (P2.1)
ROW2: J103_1.3, U102.23 (P2.2)
ROW3: J103_1.4, U102.24 (P2.3)
ROW4: J103_2.1, U102.35 (P2.4)
ROW5: J103_2.2, U102.36 (P2.5)
ROW6: J103_2.3, U102.37 (P2.6)
ROW7: J103_2.4, JP25.1 (A), U102.38 (P2.7)
SVC: J3.4, U1.24 (SWCLK)
SVD: J3.5, U1.25 (SWD)
T0: JP19.1 (A), U102.1 (T0)
T1: JP18.1 (A), U102.39 (T1)
VBUS: F17.1, J1.A4 (VBUS), J1.A9 (VBUS), J1.B4 (VBUS), J1.B9 (VBUS)
WRITE: JP20.1 (A), U102.10 (~WR)
XIN: C20.2, U1.20 (XIN), Y1.3
XOUT: R7.2, U1.21 (XOUT)

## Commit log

2024-02-20 wip: remove +5v line
2024-02-20 wip: footprint and symbols update 1
2024-02-20 wip: update footprint in pcb
2024-02-21 pcb diode 1,2 row placement
2024-02-21 wip: columns preparing
2024-02-21 wip: pcb tuning
2024-02-21 wip: pcb tuning row1 and row6 with diodes
2024-02-22 wip: pcb tuning ROW2 and ROW3 with diodes
2024-02-22 wip: all D placed near SW, fixed Nets
2024-02-22 wip: remove disturbing tracks, fix error and tuning placements
2024-02-23 wip: big matrix fix and starting routing
2024-02-23 wip: small matrix fix and continue routing
2024-02-23 wip: libraray contains several mx sizes now
2024-02-24 wip: remap and libs
2024-02-24 remap
2024-02-25 two rows
2024-02-25 switch to kicad 8.0
2024-02-25 wip: frame sch
2024-02-25 3rd row
2024-02-25 3rd row fixes
2024-02-25 wip: matrix scheme refactored
2024-02-25 add some conventional modifiers
2024-02-26 RP2040 added
2024-02-26 wip: pcb updates
2024-02-26 placer
2024-02-26 wip: placer updated
2024-02-26 deps
2024-02-26 wip: re-placer
2024-02-27 wip: dag
2024-02-28 wip: dag building, prepare for replace coords
2024-03-01 wip: top chains
2024-03-01 wip: top chains fix
2024-03-01 wip: get base coords
2024-03-01 wip: refactoring
2024-03-01 wip: refactoring2
2024-03-01 switch when to if
2024-03-01 bug fixes + commnets
2024-03-01 wip: replace coords
2024-03-02 wip: calculate coords + print into file
2024-03-09 wip: fix units, added commets, added todos
2024-03-09 ready replacer
2024-03-09 wip:changes
2024-03-09 renew pcb
2024-03-10 wip: sch fixes
2024-03-15 wip: lib
2024-03-15 wip: new buttons
2024-03-15 test
2024-03-16 wip: pcb ident test.pcb
2024-03-18 wip: dxf
2024-03-20 wip: pcb+hypo
2024-03-20 wip: tkl-backspace
2024-03-21 fix backspace
2024-03-21 fix: right shift front, add img/layout.png
2024-03-22 fixes: bottom line and backspace, keyboard-layout.json added (keyboard-layout-editor.com)
2024-03-22 wip: keyboard-layout.json updated with hypotenar
2024-03-22 wip: display2004 added, fixed to original SpaceCadet layout
2024-03-22 -1 mm horisontal display size
2024-03-25 wip: gerber layear is B_Fab now, descrease size to A4
2024-03-27 wip: rpi-pico added
2024-03-28 wip: wiring begin
2024-03-28 wip: continue wiring
2024-03-29 wip: wiring
2024-03-29 wip: wiring 2
2024-03-29 wip:wiring_3
2024-03-29 wip:wiring_4
2024-03-29 wip:wiring_5
2024-03-30 wip: schematic refactor
2024-03-30 wip: scheme refactoring
2024-03-30 wip: split schematic
2024-03-31 wip: unsplit & rewiring
2024-03-31 wip: handwiring
2024-03-31 SWMXK lib
2024-03-31 upd: diode footprint
2024-03-31 upd: RPI footprint
2024-04-01 switched fab decreased by 0.1 mm
2024-04-01 wip: renew
2024-04-01 imp: vcc & gnd added
2024-04-01 wip: rpi pico on pcb
2024-04-01 wip: pri fully connected with test points
2024-04-01 fix: unconnected
2024-04-01 imp: via test points pcb
2024-04-02 test: for gbr
2024-04-03 fix: bigger borders
2024-04-12 wip: stabs for 2u
2024-04-15 wip: stabs footprint
2024-04-15 wip: lcd +1mm
2024-04-15 upd: dxf current
2024-04-15 wip: 2u stubs ajucting
2024-04-20 fix: END btn change footprint 1u -> 2u
2024-04-21 wip: 2u little free
2024-04-21 wip: F.Courtyard layes dedicated for hotswap
2024-04-21 wip: remove unused npth pads from 2u footprint
2024-09-02 narrowing stubs for 2u bnts
2024-09-02 remove screen and compactification
2024-09-02 compact size
2024-09-04 stabs near to btn 0.15mm
